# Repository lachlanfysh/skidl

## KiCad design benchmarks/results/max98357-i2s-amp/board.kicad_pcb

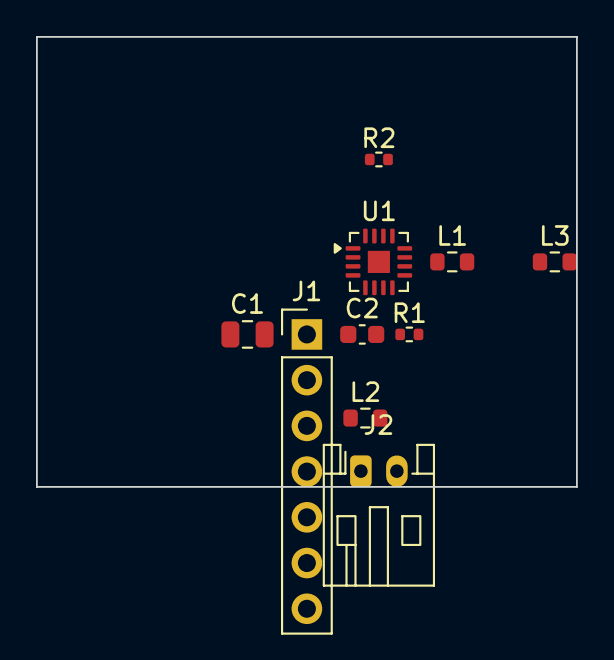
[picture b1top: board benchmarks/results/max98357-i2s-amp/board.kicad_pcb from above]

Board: 2 copper layers, 30.0 x 25.0 mm, 10 parts (0 on the bottom side), 9 nets, no tracks yet.

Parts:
C1: 10uF; C_0805_2012Metric
C2: 100nF; C_0603_1608Metric
J1: I2S_Header; PinHeader_1x07_P2.54mm_Vertical
J2: Speaker; JST_PH_S2B-PH-K_1x02_P2.00mm_Horizontal
L1, L2, L3: FB_600R; R_0603_1608Metric
R1, R2: 100K; R_0402_1005Metric
U1: MAX98357A; TQFN-16-1EP_3x3mm_P0.5mm_EP1.23x1.23mm

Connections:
BCLK: J1.4, U1.16
DIN: J1.3, U1.1
GAIN_SLOT: J1.6, R2.1, U1.2
GND: C1.2, C2.2, J1.2, R2.2, U1.3, U1.11, U1.15, U1.17
LRCLK: J1.5, U1.14
OUTN: J2.2, L3.1, L3.2, U1.10
OUTP: J2.1, L2.1, L2.2, U1.9
SD_MODE: J1.7, R1.2, U1.4
VDD: C1.1, C2.1, J1.1, L1.1, L1.2, R1.1, U1.7, U1.8

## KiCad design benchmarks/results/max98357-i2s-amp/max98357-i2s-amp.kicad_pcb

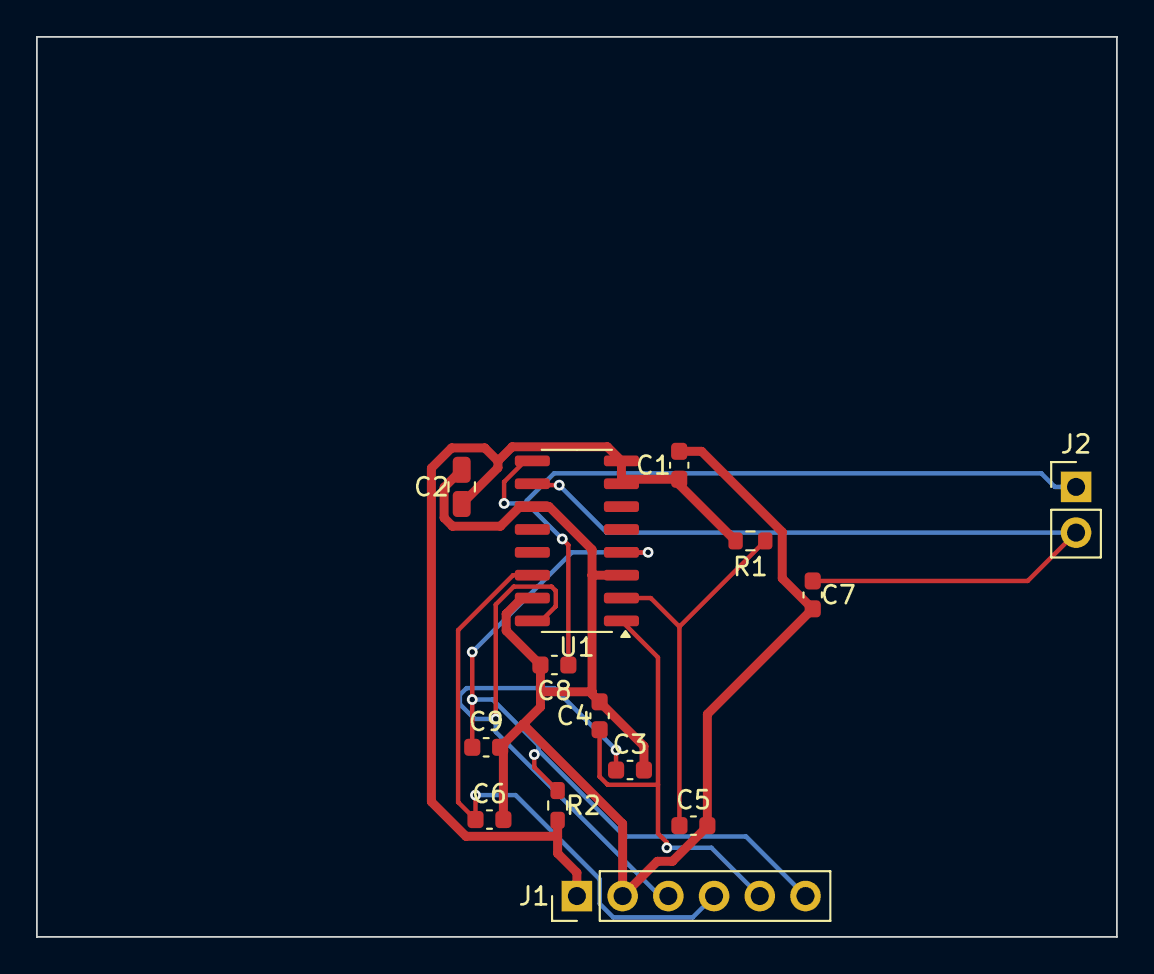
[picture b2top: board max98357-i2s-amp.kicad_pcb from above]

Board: 2 copper layers, 60.0 x 50.0 mm, 14 parts (0 on the bottom side), 9 nets.

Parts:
C1, C3, C4, C5, C6, C7, C8, C9: 100nF; C_0603_1608Metric
C2: 10uF; C_0805_2012Metric
J1: Conn_01x06; PinHeader_1x06_P2.54mm_Vertical
J2: Conn_01x02; PinHeader_1x02_P2.54mm_Vertical
R1, R2: 100K; R_0603_1608Metric
U1: MAX98357A; SOIC-16_3.9x9.9mm_P1.27mm

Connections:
BCLK: C3.1, J1.3, U1.16
DIN: C4.1, J1.5, U1.1
GAIN_SLOT: C5.1, R1.1, U1.2
GND: C1.2, C2.2, C3.2, C4.2, C5.2, C6.2, C7.2, C8.2, C9.2, J1.2, U1.3, U1.11, U1.15
LRCLK: C6.1, J1.4, U1.14
OUTN: C7.1, J2.2, U1.10
OUTP: C8.1, J2.1, U1.9
SD_MODE: C9.1, J1.6, R2.1, U1.4
VDD: C1.1, C2.1, J1.1, R1.2, R2.2, U1.7, U1.8

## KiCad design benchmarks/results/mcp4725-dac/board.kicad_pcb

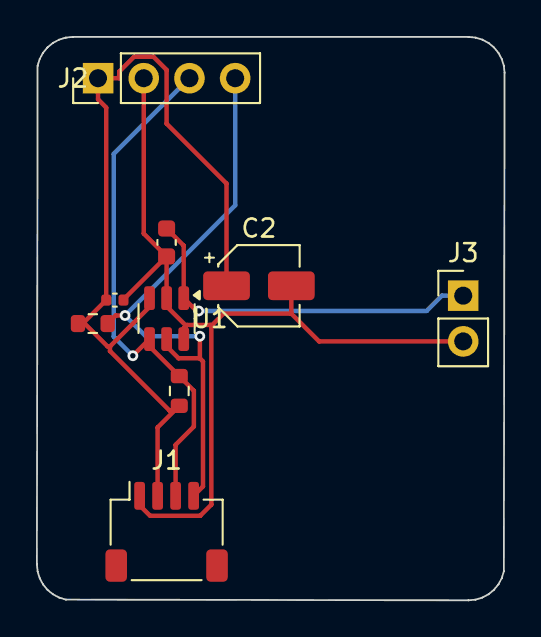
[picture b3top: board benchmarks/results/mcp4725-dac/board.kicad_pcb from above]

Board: 2 copper layers, 26.0 x 31.3 mm, 9 parts (0 on the bottom side), 5 nets.

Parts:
C1: 100nF; C_0402_1005Metric
C2: 10uF; CP_Elec_4x5.4
C3: 100nF; C_0603_1608Metric
J1: Conn_01x04_Pin; JST_SH_SM04B-SRSS-TB_1x04-1MP_P1.00mm_Horizontal
J2: Conn_01x04_Pin; PinHeader_1x04_P2.54mm_Vertical
J3: Conn_01x02_Pin; PinHeader_1x02_P2.54mm_Vertical
R1, R2: 4.7K; R_0603_1608Metric
U1: MCP4725A0T-E/CH; SOT-23-6

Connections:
GND: C1.2, C2.2, C3.2, J1.1, J2.2, J3.2, U1.2, U1.6
SCL: J1.4, J2.4, R2.2, U1.5
SDA: J1.3, J2.3, R1.2, U1.4
VCC: C1.1, C2.1, J1.2, J2.1, R1.1, R2.1, U1.3
VOUT: C3.1, J3.1, U1.1

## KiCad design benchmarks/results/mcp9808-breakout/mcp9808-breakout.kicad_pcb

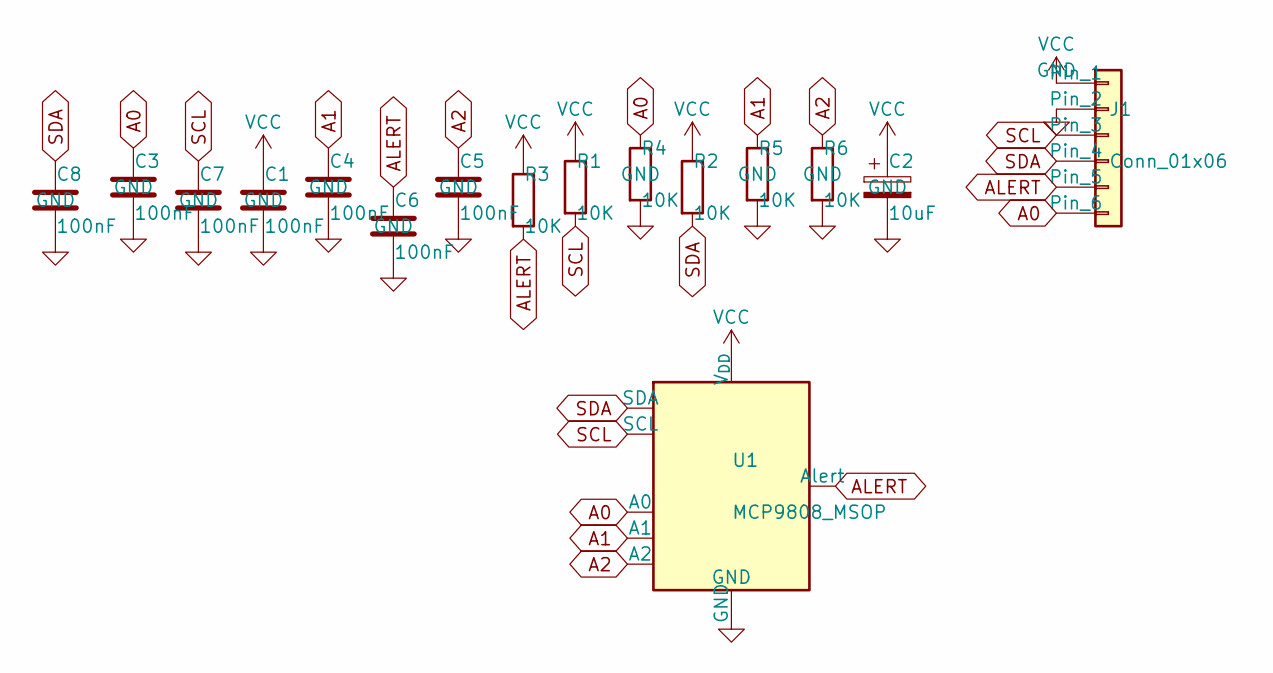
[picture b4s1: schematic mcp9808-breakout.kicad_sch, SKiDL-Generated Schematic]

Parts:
C1, C3, C4, C5, C6, C7, C8: 100nF; C_0603_1608Metric
C2: 10uF; C_0805_2012Metric
J1: Conn_01x06; PinHeader_1x06_P2.54mm_Vertical
R1, R2, R3, R4, R5, R6: 10K; R_0603_1608Metric
U1: MCP9808_MSOP; MSOP-8_3x3mm_P0.65mm

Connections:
A0: C3.1, J1.6, R4.1, U1.7 (A0)
A1: C4.1, R5.1, U1.6 (A1)
A2: C5.1, R6.1, U1.5 (A2)
ALERT: C6.1, J1.5, R3.2, U1.3 (Alert)
GND: C1.2, C2.2, C3.2, C4.2, C5.2, C6.2, C7.2, C8.2, J1.2, R4.2, R5.2, R6.2, U1.4 (GND)
SCL: C7.1, J1.3, R1.2, U1.2 (SCL)
SDA: C8.1, J1.4, R2.2, U1.1 (SDA)
VCC: C1.1, C2.1, J1.1, R1.1, R2.1, R3.1, U1.8 (V_{DD})

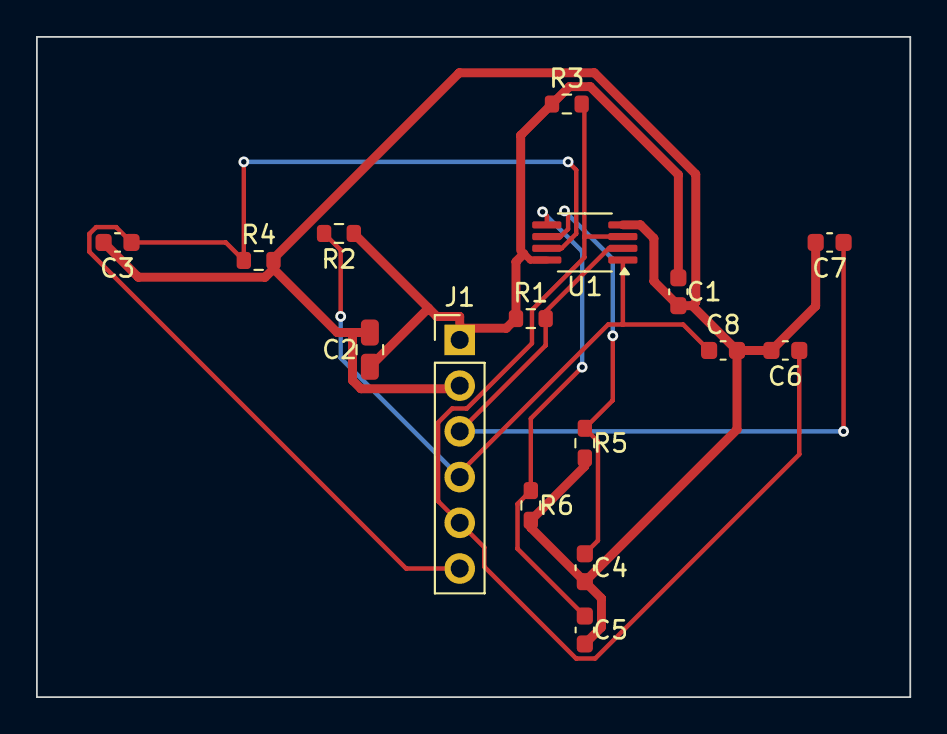
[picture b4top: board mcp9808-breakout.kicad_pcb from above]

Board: 2 copper layers, 48.5 x 36.7 mm, 16 parts (0 on the bottom side), 8 nets.

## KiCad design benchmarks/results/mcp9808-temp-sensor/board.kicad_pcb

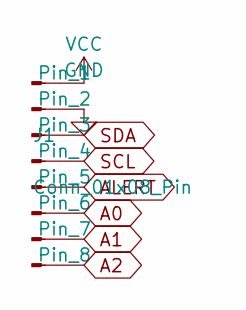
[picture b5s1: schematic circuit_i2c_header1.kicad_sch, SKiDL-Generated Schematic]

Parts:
J1: Conn_01x08_Pin; PinHeader_1x08_P2.54mm_Vertical

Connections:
A0: J1.6; also elsewhere on the board
A1: J1.7; also elsewhere on the board
A2: J1.8; also elsewhere on the board
ALERT: J1.5; also elsewhere on the board
GND: J1.2; also elsewhere on the board
SCL: J1.4; also elsewhere on the board
SDA: J1.3; also elsewhere on the board
VCC: J1.1; also elsewhere on the board

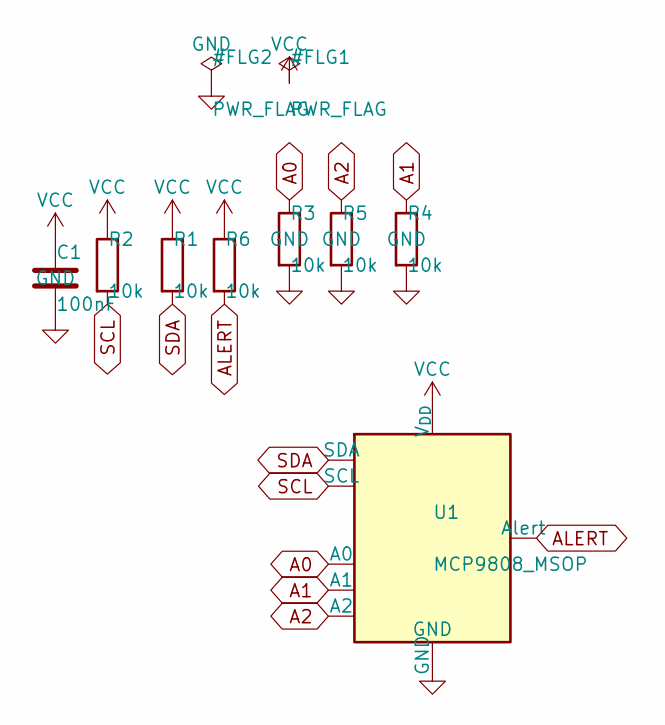
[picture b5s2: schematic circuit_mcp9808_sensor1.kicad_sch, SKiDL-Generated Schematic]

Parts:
C1: 100nF; C_0402_1005Metric
R1, R2, R3, R4, R5, R6: 10k; R_0402_1005Metric
U1: MCP9808_MSOP; MSOP-8_3x3mm_P0.65mm

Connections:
A0: R3.1, U1.7 (A0); also elsewhere on the board
A1: R4.1, U1.6 (A1); also elsewhere on the board
A2: R5.1, U1.5 (A2); also elsewhere on the board
ALERT: R6.2, U1.3 (Alert); also elsewhere on the board
GND: C1.2, R3.2, R4.2, R5.2, U1.4 (GND); also elsewhere on the board
SCL: R2.2, U1.2 (SCL); also elsewhere on the board
SDA: R1.2, U1.1 (SDA); also elsewhere on the board
VCC: C1.1, R1.1, R2.1, R6.1, U1.8 (V_{DD}); also elsewhere on the board

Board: 2 copper layers, 9 parts (0 on the bottom side), 8 nets, no tracks yet.

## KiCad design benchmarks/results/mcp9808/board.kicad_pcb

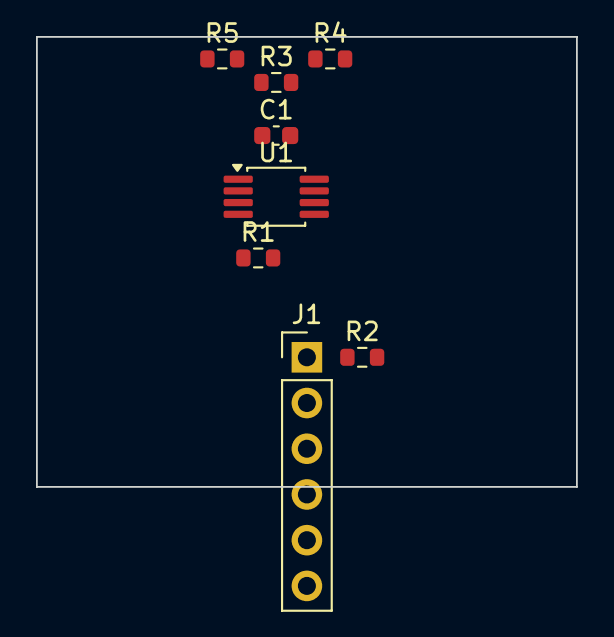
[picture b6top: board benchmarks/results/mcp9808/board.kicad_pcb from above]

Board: 2 copper layers, 30.0 x 25.0 mm, 8 parts (0 on the bottom side), 8 nets, no tracks yet.

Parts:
C1: 100nF; C_0603_1608Metric
J1: Conn_01x06; PinHeader_1x06_P2.54mm_Vertical
R1, R2, R3, R4, R5: 10K; R_0603_1608Metric
U1: MCP9808_MSOP; MSOP-8_3x3mm_P0.65mm

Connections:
ALERT: J1.5, U1.3
GND: C1.2, J1.2, J1.6, R3.2, R4.2, R5.2, U1.4
unnamed: R3.1, U1.7
unnamed: R4.1, U1.6
unnamed: R5.1, U1.5
SCL: J1.4, R2.2, U1.2
SDA: J1.3, R1.2, U1.1
VDD: C1.1, J1.1, R1.1, R2.1, U1.8

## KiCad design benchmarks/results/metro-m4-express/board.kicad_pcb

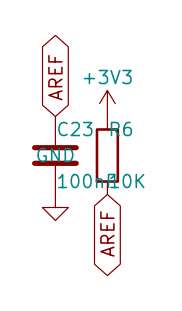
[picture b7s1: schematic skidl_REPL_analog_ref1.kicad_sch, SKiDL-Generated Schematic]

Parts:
C23: 100nF; C_0603_1608Metric
R6: 10K; R_0603_1608Metric

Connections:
+3V3: R6.1; also elsewhere on the board
AREF: C23.1, R6.2; also elsewhere on the board
GND: C23.2; also elsewhere on the board

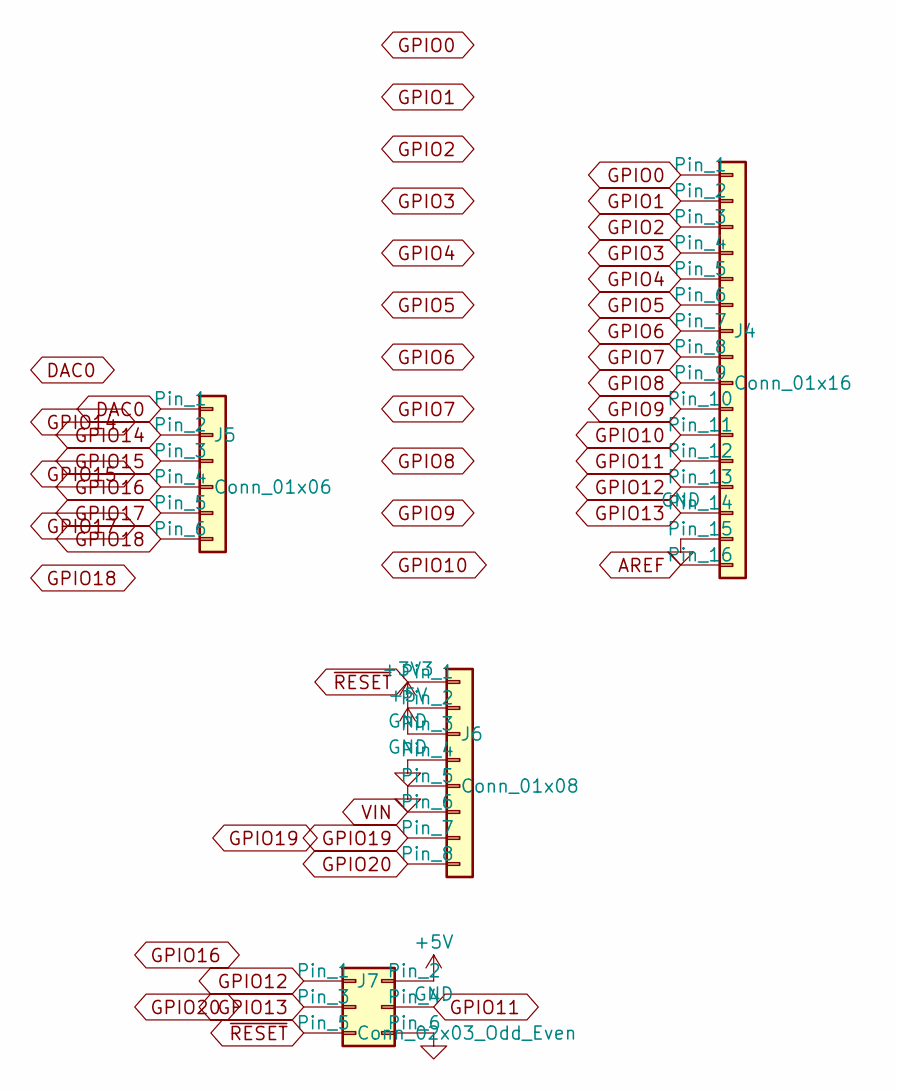
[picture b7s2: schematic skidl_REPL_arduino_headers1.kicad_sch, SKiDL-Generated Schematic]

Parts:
J4: Conn_01x16; PinHeader_1x16_P2.54mm_Vertical
J5: Conn_01x06; PinHeader_1x06_P2.54mm_Vertical
J6: Conn_01x08; PinHeader_1x08_P2.54mm_Vertical
J7: Conn_02x03_Odd_Even; PinHeader_2x03_P2.54mm_Vertical

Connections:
+3V3: J6.2; also elsewhere on the board
+5V: J6.3, J7.2; also elsewhere on the board
AREF: J4.16; also elsewhere on the board
DAC0: J5.1; also elsewhere on the board
GND: J4.15, J6.4, J6.5, J7.6; also elsewhere on the board
GPIO0: J4.1; also elsewhere on the board
GPIO1: J4.2; also elsewhere on the board
GPIO2: J4.3; also elsewhere on the board
GPIO3: J4.4; also elsewhere on the board
GPIO4: J4.5; also elsewhere on the board
GPIO5: J4.6; also elsewhere on the board
GPIO6: J4.7; also elsewhere on the board
GPIO7: J4.8; also elsewhere on the board
GPIO8: J4.9; also elsewhere on the board
GPIO9: J4.10; also elsewhere on the board
GPIO10: J4.11; also elsewhere on the board
GPIO11: J4.12, J7.4; also elsewhere on the board
GPIO12: J4.13, J7.1; also elsewhere on the board
GPIO13: J4.14, J7.3; also elsewhere on the board
GPIO14: J5.2; also elsewhere on the board
GPIO15: J5.3; also elsewhere on the board
GPIO16: J5.4; also elsewhere on the board
GPIO17: J5.5; also elsewhere on the board
GPIO18: J5.6; also elsewhere on the board
GPIO19: J6.7; also elsewhere on the board
GPIO20: J6.8; also elsewhere on the board
VIN: J6.6; also elsewhere on the board
~RESET: J6.1, J7.5; also elsewhere on the board

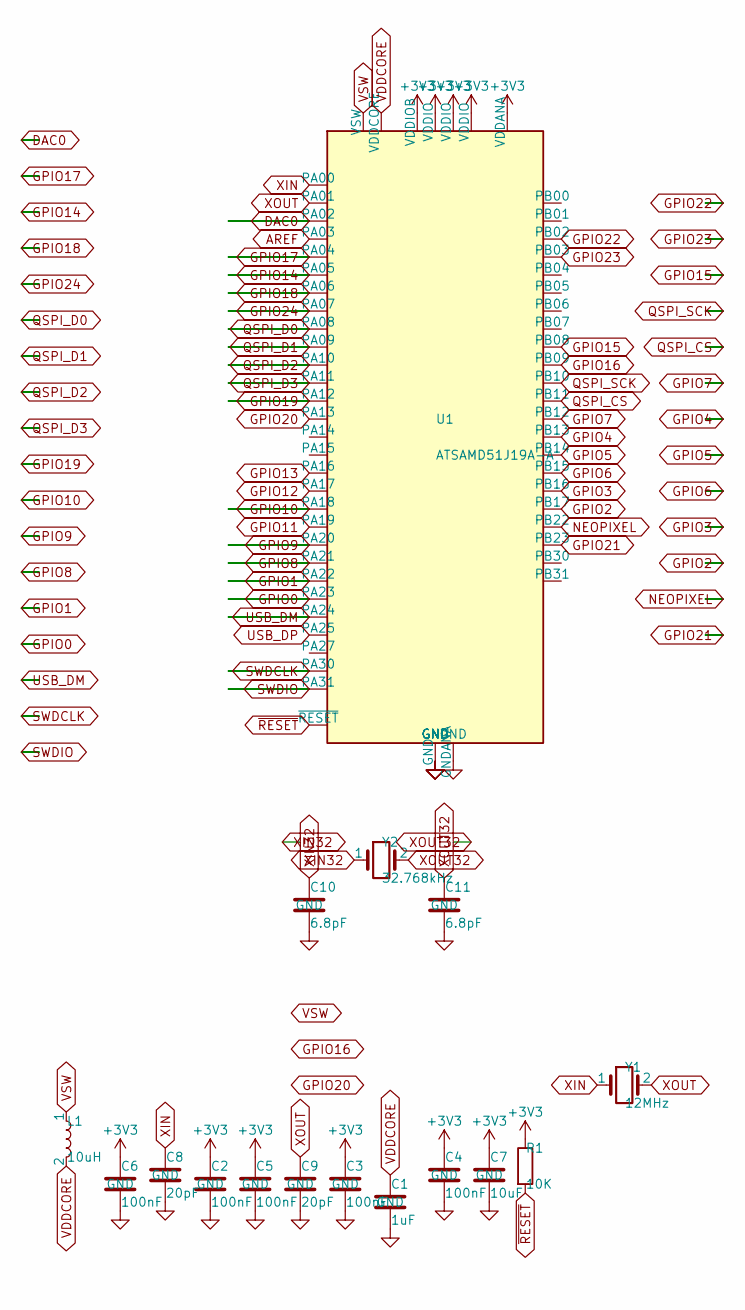
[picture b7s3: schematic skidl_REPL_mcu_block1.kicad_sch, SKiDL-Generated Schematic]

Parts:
C1: 1uF; C_0603_1608Metric
C2, C3, C4, C5, C6: 100nF; C_0603_1608Metric
C7: 10uF; C_0805_2012Metric
C8, C9: 20pF; C_0603_1608Metric
C10, C11: 6.8pF; C_0603_1608Metric
L1: 10uH; L_0805_2012Metric
R1: 10K; R_0603_1608Metric
U1: ATSAMD51J19A-A; TQFP-64_10x10mm_P0.5mm
Y1: 12MHz; Crystal_SMD_3215-2Pin_3.2x1.5mm
Y2: 32.768kHz; Crystal_SMD_2012-2Pin_2.0x1.2mm

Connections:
+3V3: C2.1, C3.1, C4.1, C5.1, C6.1, C7.1, R1.1, U1.8 (VDDANA), U1.21 (VDDIOB), U1.34 (VDDIO), U1.48 (VDDIO), U1.56 (VDDIO); also elsewhere on the board
AREF: U1.4 (PA03); also elsewhere on the board
DAC0: U1.3 (PA02); also elsewhere on the board
GND: C1.2, C2.2, C3.2, C4.2, C5.2, C6.2, C7.2, C8.2, C9.2, C10.2, C11.2, U1.7 (GNDANA), U1.22 (GND), U1.33 (GND), U1.47 (GND), U1.54 (GND); also elsewhere on the board
GPIO0: U1.44 (PA23); also elsewhere on the board
GPIO1: U1.43 (PA22); also elsewhere on the board
GPIO2: U1.40 (PB17); also elsewhere on the board
GPIO3: U1.39 (PB16); also elsewhere on the board
GPIO4: U1.26 (PB13); also elsewhere on the board
GPIO5: U1.27 (PB14); also elsewhere on the board
GPIO6: U1.28 (PB15); also elsewhere on the board
GPIO7: U1.25 (PB12); also elsewhere on the board
GPIO8: U1.42 (PA21); also elsewhere on the board
GPIO9: U1.41 (PA20); also elsewhere on the board
GPIO10: U1.37 (PA18); also elsewhere on the board
GPIO11: U1.38 (PA19); also elsewhere on the board
GPIO12: U1.36 (PA17); also elsewhere on the board
GPIO13: U1.35 (PA16); also elsewhere on the board
GPIO14: U1.14 (PA05); also elsewhere on the board
GPIO15: U1.11 (PB08); also elsewhere on the board
GPIO16: U1.12 (PB09); also elsewhere on the board
GPIO17: U1.13 (PA04); also elsewhere on the board
GPIO18: U1.15 (PA06); also elsewhere on the board
GPIO19: U1.29 (PA12); also elsewhere on the board
GPIO20: U1.30 (PA13); also elsewhere on the board
GPIO21: U1.50 (PB23)
GPIO22: U1.63 (PB02)
GPIO23: U1.64 (PB03)
GPIO24: U1.16 (PA07)
NEOPIXEL: U1.49 (PB22); also elsewhere on the board
QSPI_CS: U1.24 (PB11); also elsewhere on the board
QSPI_D0: U1.17 (PA08); also elsewhere on the board
QSPI_D1: U1.18 (PA09); also elsewhere on the board
QSPI_D2: U1.19 (PA10); also elsewhere on the board
QSPI_D3: U1.20 (PA11); also elsewhere on the board
QSPI_SCK: U1.23 (PB10); also elsewhere on the board
SWDCLK: U1.57 (PA30); also elsewhere on the board
SWDIO: U1.58 (PA31); also elsewhere on the board
USB_DM: U1.45 (PA24); also elsewhere on the board
USB_DP: U1.46 (PA25); also elsewhere on the board
VDDCORE: C1.1, L1.2, U1.53 (VDDCORE)
VSW: L1.1, U1.55 (VSW)
XIN: C8.1, U1.1 (PA00), Y1.1
XIN32: C10.1, Y2.1
XOUT: C9.1, U1.2 (PA01), Y1.2
XOUT32: C11.1, Y2.2
~RESET: R1.2, U1.52 (~RESET); also elsewhere on the board

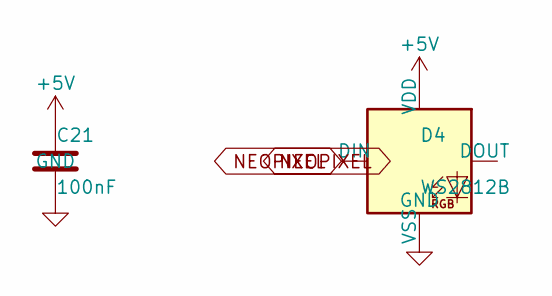
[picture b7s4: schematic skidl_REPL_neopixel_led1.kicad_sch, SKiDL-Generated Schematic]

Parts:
C21: 100nF; C_0603_1608Metric
D4: WS2812B; LED_WS2812B_PLCC4_5.0x5.0mm_P3.2mm

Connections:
+5V: C21.1, D4.1 (VDD); also elsewhere on the board
GND: C21.2, D4.3 (VSS); also elsewhere on the board
NEOPIXEL: D4.4 (DIN); also elsewhere on the board

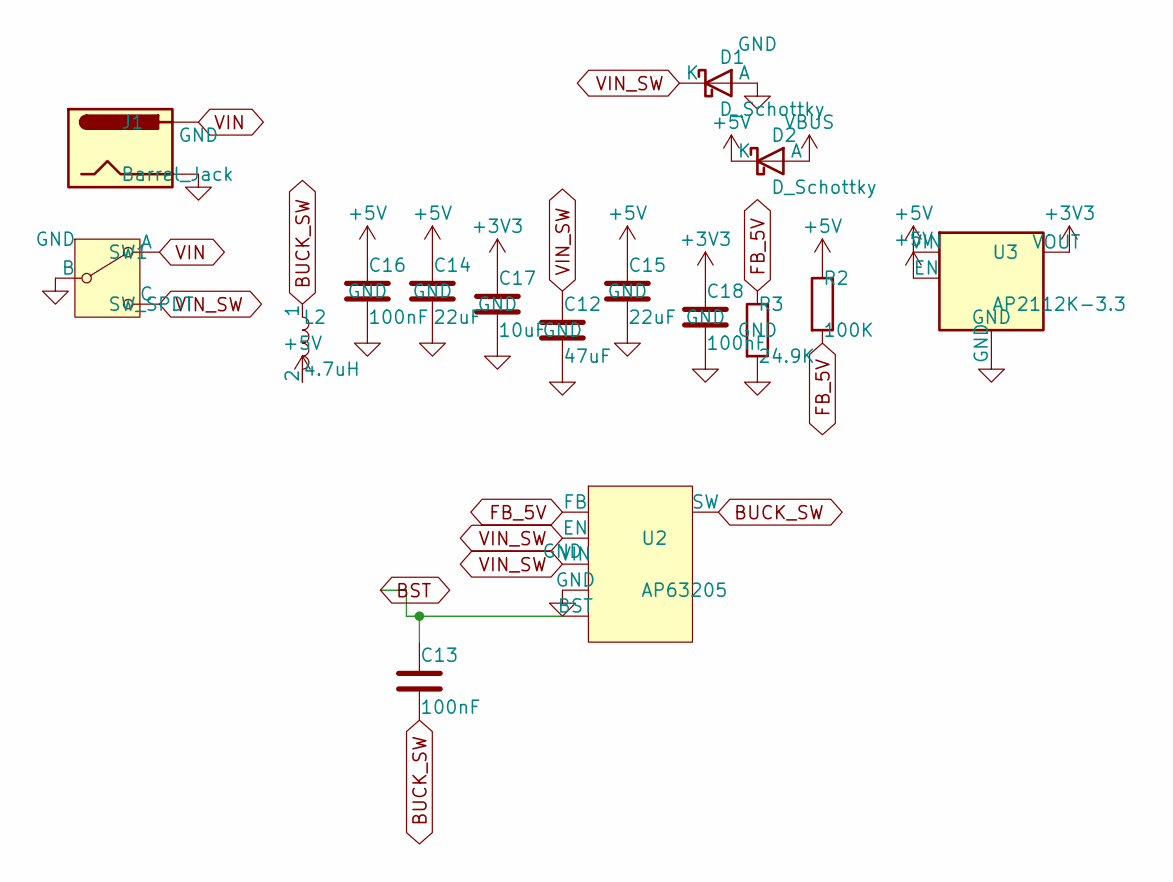
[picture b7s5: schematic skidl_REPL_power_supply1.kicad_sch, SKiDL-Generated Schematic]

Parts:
C12: 47uF; C_0805_2012Metric
C13, C16, C18: 100nF; C_0603_1608Metric
C14, C15: 22uF; C_0805_2012Metric
C17: 10uF; C_0805_2012Metric
D1, D2: D_Schottky; D_SMA
J1: Barrel_Jack; BarrelJack_CUI_PJ-063AH_Horizontal
L2: 4.7uH; L_0805_2012Metric
R2: 100K; R_0603_1608Metric
R3: 24.9K; R_0603_1608Metric
SW1: SW_SPDT; SW_DIP_SPSTx01_Slide_6.7x4.1mm_W8.61mm_P2.54mm_LowProfile
U2: AP63205; SOT-23-6
U3: AP2112K-3.3; SOT-23-5

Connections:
+3V3: C17.1, C18.1, U3.5 (VOUT); also elsewhere on the board
+5V: C14.1, C15.1, C16.1, D2.1 (K), L2.2, R2.1, U3.1 (VIN), U3.3 (EN); also elsewhere on the board
BST: C13.1, U2.6 (BST)
BUCK_SW: C13.2, L2.1, U2.5 (SW)
FB_5V: R2.2, R3.1, U2.1 (FB)
GND: C12.2, C14.2, C15.2, C16.2, C17.2, C18.2, D1.2 (A), J1.2, R3.2, SW1.2 (B), U2.4 (GND), U3.2 (GND); also elsewhere on the board
VBUS: D2.2 (A); also elsewhere on the board
VIN: J1.1, SW1.1 (A); also elsewhere on the board
VIN_SW: C12.1, D1.1 (K), SW1.3 (C), U2.2 (EN), U2.3 (VIN)

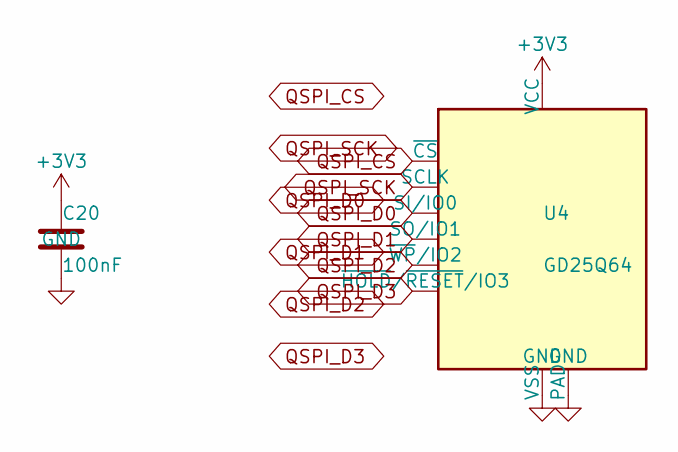
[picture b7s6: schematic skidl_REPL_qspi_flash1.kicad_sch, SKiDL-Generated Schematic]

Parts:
C20: 100nF; C_0603_1608Metric
U4: GD25Q64; SOIC-8_3.9x4.9mm_P1.27mm

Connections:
+3V3: C20.1, U4.8 (VCC); also elsewhere on the board
GND: C20.2, U4.4 (VSS), U4.9 (PAD); also elsewhere on the board
QSPI_CS: U4.1 (~CS); also elsewhere on the board
QSPI_D0: U4.5 (SI/IO0); also elsewhere on the board
QSPI_D1: U4.2 (SO/IO1); also elsewhere on the board
QSPI_D2: U4.3 (~WP/IO2); also elsewhere on the board
QSPI_D3: U4.7 (~HOLD/~RESET/IO3); also elsewhere on the board
QSPI_SCK: U4.6 (SCLK); also elsewhere on the board

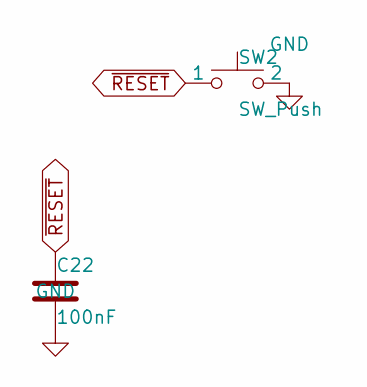
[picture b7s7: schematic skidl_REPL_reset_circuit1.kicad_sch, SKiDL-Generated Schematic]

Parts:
C22: 100nF; C_0603_1608Metric
SW2: SW_Push; SW_DIP_SPSTx01_Slide_6.7x4.1mm_W8.61mm_P2.54mm_LowProfile

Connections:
GND: C22.2, SW2.2; also elsewhere on the board
~RESET: C22.1, SW2.1; also elsewhere on the board

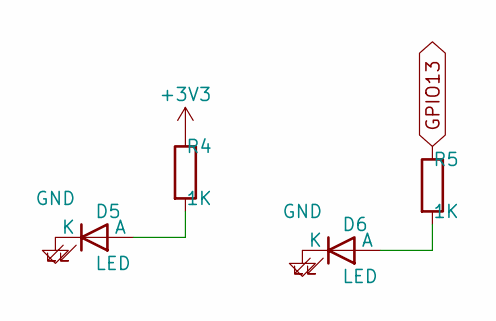
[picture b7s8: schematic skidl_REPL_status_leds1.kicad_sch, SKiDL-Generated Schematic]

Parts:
D5, D6: LED; LED_0603_1608Metric
R4, R5: 1K; R_0603_1608Metric

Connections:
+3V3: R4.1; also elsewhere on the board
GND: D5.1 (K), D6.1 (K); also elsewhere on the board
GPIO13: R5.1; also elsewhere on the board
unnamed: D5.2 (A), R4.2
unnamed: D6.2 (A), R5.2

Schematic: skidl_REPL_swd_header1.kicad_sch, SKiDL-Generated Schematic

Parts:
J3: Conn_02x05_Odd_Even; PinHeader_2x05_P1.27mm_Vertical

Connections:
+3V3: J3.1; also elsewhere on the board
GND: J3.3, J3.5, J3.6, J3.7, J3.8, J3.9; also elsewhere on the board
SWDCLK: J3.4; also elsewhere on the board
SWDIO: J3.2; also elsewhere on the board
~RESET: J3.10; also elsewhere on the board

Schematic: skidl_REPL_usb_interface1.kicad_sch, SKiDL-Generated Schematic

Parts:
C19: 100nF; C_0603_1608Metric
D3: D_TVS; D_SMA
J2: USB_B_Micro; USB_Micro-B_Molex-105017-0001

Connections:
GND: C19.2, D3.2 (A2), J2.5 (GND), J2.6 (Shield); also elsewhere on the board
USB_DM: J2.2 (D-); also elsewhere on the board
USB_DP: D3.1 (A1), J2.3 (D+); also elsewhere on the board
VBUS: C19.1, J2.1 (VBUS); also elsewhere on the board

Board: 2 copper layers, 52 parts (0 on the bottom side), 52 nets, no tracks yet.

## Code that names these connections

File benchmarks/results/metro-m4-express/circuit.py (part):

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    c_vcore[1] += vcore_net
    c_vcore[2] += gnd

    # VSW (pin 55) - switching regulator inductor
    vsw_net = Net("VSW")
    mcu["VSW"] += vsw_net
    l_vsw = Part("Device", "L", value="10uH",
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    c_bulk[1] += v3v3
    c_bulk[2] += gnd

    # USB (PA24=D-, PA25=D+)
    mcu["PA24"] += usb_dm
    mcu["PA25"] += usb_dp

    # Reset with pull-up
    mcu["~{RESET}"] += reset_n
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    r_rst[1] += v3v3
    r_rst[2] += reset_n

    # Main crystal 12MHz (PA00=XIN, PA01=XOUT)
    y1 = Part("Device", "Crystal", value="12MHz",
              footprint="Crystal:Crystal_SMD_3215-2Pin_3.2x1.5mm")
    y1[1] += xin
    y1[2] += xout
    mcu["PA00"] += xin
    mcu["PA01"] += xout

    c_xin = Part("Device", "C", value="20pF",
                 footprint="Capacitor_SMD:C_0603_1608Metric")
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    c_xout32[2] += gnd

    # SWD debug
    mcu["PA30"] += swdclk
    mcu["PA31"] += swdio

    # AREF
    mcu["PA03"] += aref

    # QSPI flash connections
    mcu["PA08"] += qspi_d0
    mcu["PA09"] += qspi_d1
    mcu["PA10"] += qspi_d2
    mcu["PA11"] += qspi_d3
    mcu["PB10"] += qspi_sck
    mcu["PB11"] += qspi_cs

    # NeoPixel (PB22 on Metro M4)
    mcu["PB22"] += neopixel_data

    # DAC output (PA02 = DAC0)
    mcu["PA02"] += dac0_out

    # GPIO pin assignments to Arduino headers
    gpio_map = {
        "PA23": 0,   # D0 (RX)
        "PA22": 1,   # D1 (TX)
        "PB17": 2,   # D2
        "PB16": 3,   # D3
        "PB13": 4,   # D4
        "PB14": 5,   # D5
        "PB15": 6,   # D6
        "PB12": 7,   # D7
        "PA21": 8,   # D8
        "PA20": 9,   # D9
        "PA18": 10,  # D10 (SS)
        "PA19": 11,  # D11 (MOSI)
        "PA17": 12,  # D12 (MISO)
        "PA16": 13,  # D13 (SCK/LED)
        "PA05": 14,  # A1
        "PB08": 15,  # A2
        "PB09": 16,  # A3
        "PA04": 17,  # A4
        "PA06": 18,  # A5
        "PA12": 19,  # SDA
        "PA13": 20,  # SCL
        "PB23": 21,  # D14/TX3
        "PB02": 22,  # D15/RX3
        "PB03": 23,  # D16
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        ("3", "VIN", Pin.types.PWRIN),
        ("4", "GND", Pin.types.PWRIN),
        ("5", "SW", Pin.types.OUTPUT),
        ("6", "BST", Pin.types.PASSIVE),
    ])
    vreg_5v["VIN"] += vin_switched
    vreg_5v["EN"] += vin_switched
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
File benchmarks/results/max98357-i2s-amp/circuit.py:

"""
MAX98357A I2S Class-D Mono Amp Breakout
========================================
All-in-one digital audio amp: I2S input -> DAC -> Class-D amplifier -> speaker.
Delivers 3.2W into 4 ohm (5V, 10% THD). VDD range 2.7V-5.5V.
Built-in filterless output, thermal and over-current protection.

Breakout design:
- USB-C (5V) power input with ferrite bead filtering
- 5-pin I2S header (VDD, GND, BCLK, LRCLK, DIN)
- Screw terminal speaker output
- 100nF x2 decoupling on VDD (auto-placed near IC)
- Gain select: 100k to VDD = 9dB (float=15dB, GND=12dB)
- SD_MODE: 100k pull-up to VDD = left channel, always-on

Part note: No KiCad symbol for MAX98357A exists in standard libs.
Symbol loaded from EasyEDA via convert_lcsc(lcsc="C910544").
Footprint substituted to KiCad standard TQFN-16-1EP_3x3mm (pin-compatible).
N.C. pads (5,6,12,13) tied to GND per TQFN best practice.
"""

from skidl import *

# Power rails
vbus = Net("VBUS"); vbus.drive = POWER
vdd = Net("VDD"); vdd.drive = POWER
gnd = Net("GND"); gnd.drive = POWER

# I2S signal nets
bclk = Net("BCLK")
lrclk = Net("LRCLK")
din = Net("DIN")

# Speaker output nets (differential, Class-D filterless)
outp = Net("OUTP")
outn = Net("OUTN")

# Gain/SD control nets
gain_slot = Net("GAIN_SLOT")
sd_mode = Net("SD_MODE")

# ---- U1: MAX98357A I2S Class-D Amplifier ----
# Symbol from EasyEDA (LCSC C910544). KiCad TQFN-16 3x3mm footprint.
u1 = Part("C910544", "MAX98357AETE+T",
          footprint="Package_DFN_QFN:TQFN-16-1EP_3x3mm_P0.5mm_EP1.6x1.6mm")

vdd += u1["VDD"]
gnd += u1["GND"], u1["EP"]
bclk += u1["BCLK"]
lrclk += u1["LRCLK"]
din += u1["DIN"]
outp += u1["OUTP"]
outn += u1["OUTN"]
gain_slot += u1["GAIN_SLOT"]
sd_mode += u1["~{SD_MODE}"]
# N.C. pads tied to GND (standard practice for unused TQFN pads)
gnd += u1[5], u1[6], u1[12], u1[13]

# ---- J1: USB-C power input (5V, up to 3A) ----
# 6P power-only symbol paired with matching 6P footprint (GCT USB4125)
j1 = Part("Connector", "USB_C_Receptacle_PowerOnly_6P",
          footprint="Connector_USB:USB_C_Receptacle_GCT_USB4125-xx-x_6P_TopMnt_Horizontal")
j1.edge_preference = "bottom"
vbus += j1["VBUS"]
gnd += j1["GND"], j1["SHIELD"]

# 5.1k CC pull-downs for USB-C 5V sink identification (no PD chip needed)
r_cc1 = Part("Device", "R", value="5.1K", footprint="Resistor_SMD:R_0402_1005Metric")
r_cc2 = Part("Device", "R", value="5.1K", footprint="Resistor_SMD:R_0402_1005Metric")
j1["CC1"] += r_cc1[1]; gnd += r_cc1[2]
j1["CC2"] += r_cc2[1]; gnd += r_cc2[2]

# ---- FB1: Ferrite bead for power supply filtering (VBUS -> VDD) ----
# 600R @ 100MHz, 0805 package for sufficient current rating (3A+)
fb1 = Part("Device", "FerriteBead", value="600R@100MHz", footprint="Resistor_SMD:R_0805_2012Metric")
vbus += fb1[1]
vdd += fb1[2]

# ---- Decoupling caps on VDD (auto-placed near U1 by layout engine) ----
c1 = Part("Device", "C", value="100nF", footprint="Capacitor_SMD:C_0402_1005Metric")
c2 = Part("Device", "C", value="100nF", footprint="Capacitor_SMD:C_0402_1005Metric")
vdd += c1[1], c2[1]
gnd += c1[2], c2[2]

# Bulk caps: VBUS input (10uF) and VDD rail (10uF)
c3 = Part("Device", "C_Polarized", value="10uF", footprint="Capacitor_SMD:C_0805_2012Metric")
c4 = Part("Device", "C_Polarized", value="10uF", footprint="Capacitor_SMD:C_0805_2012Metric")
vbus += c3[1]; gnd += c3[2]
vdd += c4[1]; gnd += c4[2]

# ---- J2: I2S input header (5-pin: VDD, GND, BCLK, LRCLK, DIN) ----
j2 = Part("Connector_Generic", "Conn_01x05",
          footprint="Connector_PinHeader_2.54mm:PinHeader_1x05_P2.54mm_Vertical")
j2.edge_preference = "top"
vdd += j2[1]; gnd += j2[2]; bclk += j2[3]; lrclk += j2[4]; din += j2[5]

# ---- J3: Speaker output screw terminal (3.5mm pitch horizontal) ----
j3 = Part("Connector", "Screw_Terminal_01x02",
          footprint="TerminalBlock_Phoenix:TerminalBlock_Phoenix_PT-1,5-2-3.5-H_1x02_P3.50mm_Horizontal")
j3.edge_preference = "top"
outp += j3[1]
outn += j3[2]

# ---- R_GAIN: Gain select (GAIN_SLOT to VDD via 100k = 9dB) ----
r_gain = Part("Device", "R", value="100K", footprint="Resistor_SMD:R_0402_1005Metric")
gain_slot += r_gain[1]; vdd += r_gain[2]

# ---- R_SD: SD_MODE pull-up (100k to VDD = left channel, always-on) ----
r_sd = Part("Device", "R", value="100K", footprint="Resistor_SMD:R_0402_1005Metric")
sd_mode += r_sd[1]; vdd += r_sd[2]

# ---- Mounting holes (M2) ----
mh1 = Part("Mechanical", "MountingHole", footprint="MountingHole:MountingHole_2.2mm_M2")
mh2 = Part("Mechanical", "MountingHole", footprint="MountingHole:MountingHole_2.2mm_M2")
mh3 = Part("Mechanical", "MountingHole", footprint="MountingHole:MountingHole_2.2mm_M2")
mh4 = Part("Mechanical", "MountingHole", footprint="MountingHole:MountingHole_2.2mm_M2")

EDA_FLOORPLAN = {
    "outline": {"width_mm": 50, "height_mm": 36, "corner_radius_mm": 1},
}
